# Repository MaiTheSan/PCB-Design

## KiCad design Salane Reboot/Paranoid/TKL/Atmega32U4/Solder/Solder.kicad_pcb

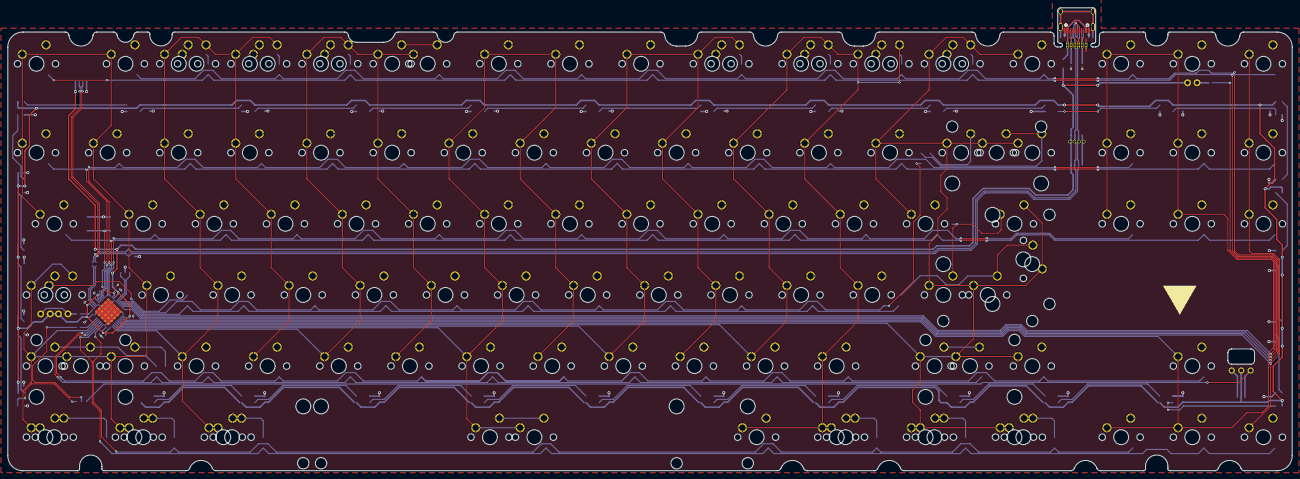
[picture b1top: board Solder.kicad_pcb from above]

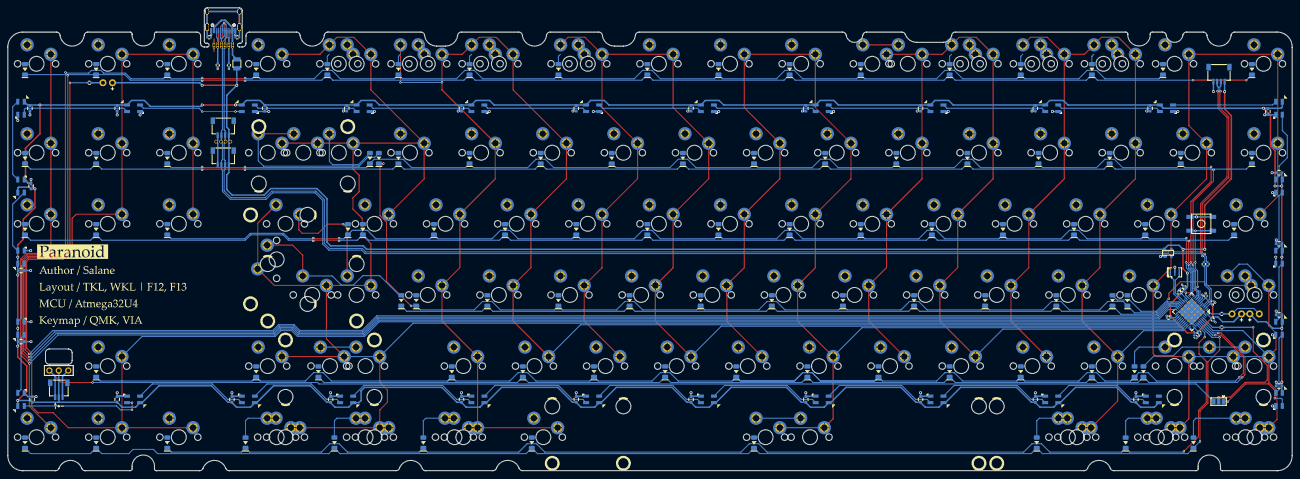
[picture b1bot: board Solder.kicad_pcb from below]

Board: 2 copper layers, 344.0 x 124.0 mm, 299 parts (181 on the bottom side), 164 nets.

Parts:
C1, C3, C4, C5, C6, C8: 0.1uF; C_0402
C2: 1uF; C_0402
C7: 10uF; C_0402
C9, C10, C11, C12, C13, C14, C15, C16, C17, C18, C19, C20, C21, C22, C23, C24, C25, C26, C27, C28, C29, C30, C31, C32, C33, C34, C35, C36, C37, C38: 0.1uF; C_0603
D1: LED; MXOnly-LEDONLY-FLIPPED
D2, D3: LED; MXOnly-LEDONLY
D4, D5, D6, D7, D8, D9, D10, D11, D12, D13, D14, D15, D16, D17, D18, D19, D20, D21, D22, D23, D24, D25, D26, D27, D28, D29, D30, D31, D32, D33, D34, D35, D36, D37, D38, D39, D40, D41, D42, D43, D44, D45, D46, D47, D48, D49, D50, D51, D52, D53, D54, D55, D56, D57, D58, D59, D60, D61, D62, D63, D64, D65, D66, D67, D68, D69, D70, D71, D72, D73, D74, D75, D76, D77, D78, D79, D80, D81, D82, D83, D84, D85, D86, D87, D88, D89, D90, D91, D92, D93, D94: 1N4148W; DIODE_1206_SawnsProjects
F1: 500mA; Fuse_SMD1206_Reflow
J1: Conn_01x06_Female; BreakoutUSB
J2: Suit; JST-SR-4
J3: HIney/Mechlovin; JST-SR-4
J4: Breakout; PinHeader_1x04_P1.27mm_Vertical
J5: Amber TKL; JST-SR-4
J6: RGB JST; JST-SR-3
J7: RGB Breakout; RGB-Header
JP1: Jumper_NC_Dual; SolderJumper-3_P1.3mm_Open_Pad1.0x1.5mm
MX1, MX4, MX17, MX73, MX91, MX99: 1.5U; MXOnly-1.5U-NoLED
MX2, MX3, MX10, MX11, MX12, MX13, MX14, MX15, MX18, MX19, MX20, MX21, MX22, MX24, MX25, MX26, MX27, MX28, MX29, MX30, MX31, MX32, MX33, MX34, MX35, MX36, MX37, MX38, MX39, MX40, MX41, MX42, MX44, MX45, MX46, MX47, MX48, MX50, MX51, MX52, MX53, MX54, MX55, MX56, MX57, MX58, MX59, MX60, MX61, MX62, MX63, MX64, MX65, MX66, MX67, MX68, MX69, MX70, MX72, MX74, MX75, MX76, MX77, MX78, MX80, MX81, MX82, MX83, MX84, MX89, MX92, MX93, MX94, MX95, MX97, MX100, MX101, MX102, MX103, MX104, MX105, MX106, MX107, MX108, MX109, MX110, MX111, MX112: 1U; MXOnly-1U-NoLED
MX5, MX6, MX8, MX16, MX23, MX71, MX79, MX88, MX98: 1.25U; MXOnly-1.25U-NoLED
MX7: 2.25U; MXOnly-2.25U-NoLED
MX9, MX86: 1.75U; MXOnly-1.75U-NoLED
MX43: 7U; MXOnly-7U-ReversedStabilizers-NoLED
MX49: 6.25U; MXOnly-6.25U-ReversedStabilizers-NoLED
MX85: 2.25U; MXOnly-2.25U-ReversedStabilizers-NoLED
MX87: 2.75U; MXOnly-2.75U-NoLED
MX90: ISO; MXOnly-ISO-ROTATED-ReversedStabilizers-NoLED
MX96: 2U; MXOnly-2U-NoLED
R1, R4: 10k; R_0402
R2, R3, R5: 300R; R_0402
R6: 1M; R_0402
R7, R8: 22R; R_0402
R9, R10: 5.1k; R_0402
RGB1, RGB2, RGB3, RGB4, RGB5, RGB6, RGB7, RGB8, RGB9, RGB10, RGB11, RGB12, RGB13, RGB14, RGB15, RGB16, RGB17, RGB18, RGB19, RGB20, RGB21, RGB22, RGB23, RGB24, RGB25, RGB26, RGB27, RGB28, RGB29, RGB30: WS2812B; LED_SK6812MINI_PLCC4_3.5x3.5mm_P1.75mm
SW1: SW_Push; SKQG-1155865-2pin
U1: ATmega32U4-MU; QFN-44-1EP_7x7mm_P0.5mm_EP5.2x5.2mm
U2: PRTR5V0U2X; SOT143B
USB1, USB2: HRO-TYPE-C-31-M-12-Type-C; HRO-TYPE-C-31-M-12-Assembly
Y1: 16MHz; Resonator_SMD_muRata_CSTxExxV-3Pin_3.0x1.1mm

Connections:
+5V: C1.1, C3.1, C4.1, C5.1, C6.1, C7.1, C9.2, C10.2, C11.2, C12.2, C13.2, C14.2, C15.2, C16.2, C17.2, C18.2, C19.1, C20.1, C21.1, C22.1, C23.1, C24.1, C25.1, C26.1, C27.1, C28.1, C29.2, C30.1, C31.2, C32.1, C33.2, C34.1, C35.2, C36.1, C37.2, C38.1, D1.2, D2.2, D3.2, F1.2, J2.1, J3.1, J4.1, J5.1, J6.2, J7.2, R1.1, RGB1.1, RGB2.1, RGB3.1, RGB4.1, RGB5.1, RGB6.1, RGB7.1, RGB8.1, RGB9.1, RGB10.1, RGB11.1, RGB12.1, RGB13.1, RGB14.1, RGB15.1, RGB16.1, RGB17.1, RGB18.1, RGB19.1, RGB20.1, RGB21.1, RGB22.1, RGB23.1, RGB24.1, RGB25.1, RGB26.1, RGB27.1, RGB28.1, RGB29.1, RGB30.1, U1.2, U1.7, U1.14, U1.24, U1.34, U1.44, U2.4
C0: MX1.1, MX2.1, MX3.1, MX4.1, MX5.1, MX6.1, MX7.1, MX8.1, MX9.2, MX10.1, MX11.1, MX12.1, MX13.1, MX14.1, MX15.1, MX16.1, U1.40
C1: MX17.1, MX18.1, MX19.1, MX20.1, MX21.1, MX22.1, MX23.1, MX24.2, MX25.1, MX26.1, MX27.1, MX28.1, MX29.1, MX30.2, U1.32
C2: MX31.1, MX32.1, MX33.1, MX34.1, MX35.1, MX36.2, MX37.1, MX38.1, MX39.1, MX40.1, MX41.1, MX42.1, U1.31
C3: MX43.1, MX44.1, MX45.1, MX46.1, MX47.1, MX48.1, MX49.1, MX50.1, MX51.1, MX52.1, MX53.1, MX54.1, U1.30
C4: MX55.1, MX56.1, MX57.1, MX58.1, MX59.1, MX60.1, MX61.1, MX62.1, MX63.1, MX64.1, MX65.2, U1.29
C5: MX66.1, MX67.1, MX68.1, MX69.1, MX70.1, MX71.1, MX72.2, MX73.1, MX74.1, MX75.1, MX76.1, MX77.1, MX78.1, MX79.1, MX80.2, U1.28
C6: MX81.1, MX82.1, MX83.1, MX84.1, MX85.1, MX86.1, MX87.1, MX88.1, MX89.2, MX90.2, MX91.1, MX92.1, MX93.1, MX94.1, MX95.1, MX96.1, MX97.1, MX98.1, MX99.2, U1.27
C7: MX100.1, MX101.1, MX102.1, MX103.1, MX104.1, MX105.1, MX106.1, MX107.1, MX108.1, U1.26
C8: MX109.1, MX110.1, MX111.1, MX112.1, U1.25
C+: J1.4, J2.3, J3.3, J4.3, J5.3, R8.1, U2.2, USB1.6, USB1.8, USB2.6, USB2.8
C-: J1.3, J2.2, J3.2, J4.2, J5.2, R7.2, U2.3, USB1.5, USB1.7, USB2.5, USB2.7
CC1: J1.2, R9.2, USB1.10, USB2.4
CC2: J1.5, R10.1, USB1.4, USB2.10
Caps: R2.1, U1.1
D+: R8.2, U1.4
D-: R7.1, U1.3
DOUT: J6.3, J7.3, JP1.3
Fuse: F1.1, J1.1, USB1.2, USB1.11, USB2.2, USB2.11
GND: C1.2, C2.1, C3.2, C4.2, C5.2, C6.2, C7.2, C8.2, C9.1, C10.1, C11.1, C12.1, C13.1, C14.1, C15.1, C16.1, C17.1, C18.1, C19.2, C20.2, C21.2, C22.2, C23.2, C24.2, C25.2, C26.2, C27.2, C28.2, C29.1, C30.2, C31.1, C32.2, C33.1, C34.2, C35.1, C36.2, C37.1, C38.2, J1.6, J2.4, J3.4, J4.4, J5.4, J6.1, J7.1, R4.1, R6.1, R9.1, R10.2, RGB1.3, RGB2.3, RGB3.3, RGB4.3, RGB5.3, RGB6.3, RGB7.3, RGB8.3, RGB9.3, RGB10.3, RGB11.3, RGB12.3, RGB13.3, RGB14.3, RGB15.3, RGB16.3, RGB17.3, RGB18.3, RGB19.3, RGB20.3, RGB21.3, RGB22.3, RGB23.3, RGB24.3, RGB25.3, RGB26.3, RGB27.3, RGB28.3, RGB29.3, RGB30.3, SW1.1, U1.5, U1.15, U1.23, U1.35, U1.43, U1.45, U2.1, USB1.1, USB1.12, USB2.1, USB2.12, Y1.2
unnamed: C2.2, U1.6
unnamed: D1.1, D2.1, R2.2
unnamed: D3.1, R3.2
unnamed: D4.2, MX2.2
unnamed: D5.2, MX3.2
unnamed: D6.2, MX4.2
unnamed: D7.2, MX5.2, MX9.1
unnamed: D8.2, MX6.2, MX7.2
unnamed: D9.2, MX1.2, MX8.2
unnamed: D10.2, MX11.2
unnamed: D11.2, MX12.2
unnamed: D12.2, MX13.2
unnamed: D13.2, MX14.2
unnamed: D14.2, MX15.2
unnamed: D15.2, MX10.2, MX16.2
unnamed: D16.2, MX18.2, MX24.1
unnamed: D17.2, MX19.2
unnamed: D18.2, MX20.2
unnamed: D19.2, MX21.2
unnamed: D20.2, MX22.2
unnamed: D21.2, MX17.2, MX23.2
unnamed: D22.2, MX25.2, MX30.1
unnamed: D23.2, MX26.2
unnamed: D24.2, MX27.2
unnamed: D25.2, MX28.2
unnamed: D26.2, MX29.2
unnamed: D27.2, MX31.2, MX36.1
unnamed: D28.2, MX32.2
unnamed: D29.2, MX33.2
unnamed: D30.2, MX34.2
unnamed: D31.2, MX35.2
unnamed: D32.2, MX37.2, MX38.2
unnamed: D33.2, MX39.2
unnamed: D34.2, MX40.2
unnamed: D35.2, MX41.2
unnamed: D36.2, MX42.2
unnamed: D37.2, MX44.2
unnamed: D38.2, MX45.2
unnamed: D39.2, MX46.2
unnamed: D40.2, MX47.2
unnamed: D41.2, MX48.2
unnamed: D42.2, MX43.2, MX49.2
unnamed: D43.2, MX50.2
unnamed: D44.2, MX51.2
unnamed: D45.2, MX52.2
unnamed: D46.2, MX53.2
unnamed: D47.2, MX54.2
unnamed: D48.2, MX55.2
unnamed: D49.2, MX56.2
unnamed: D50.2, MX57.2
unnamed: D51.2, MX58.2
unnamed: D52.2, MX59.2
unnamed: D53.2, MX60.2, MX65.1
unnamed: D54.2, MX61.2
unnamed: D55.2, MX62.2
unnamed: D56.2, MX63.2
unnamed: D57.2, MX64.2
unnamed: D58.2, MX66.2, MX72.1
unnamed: D59.2, MX67.2
unnamed: D60.2, MX68.2
unnamed: D61.2, MX69.2
unnamed: D62.2, MX70.2
unnamed: D63.2, MX71.2
unnamed: D64.2, MX74.2, MX80.1
unnamed: D65.2, MX75.2
unnamed: D66.2, MX76.2
unnamed: D67.2, MX77.2
unnamed: D68.2, MX78.2
unnamed: D69.2, MX73.2, MX79.2
unnamed: D70.2, MX82.2, MX89.1
unnamed: D71.2, MX83.2
unnamed: D72.2, MX84.2
unnamed: D73.2, MX85.2, MX90.1
unnamed: D74.2, MX86.2, MX87.2
unnamed: D75.2, MX81.2, MX88.2
unnamed: D76.2, MX92.2
unnamed: D77.2, MX93.2
unnamed: D78.2, MX94.2, MX99.1
unnamed: D79.2, MX95.2, MX96.2
unnamed: D80.2, MX97.2
unnamed: D81.2, MX91.2, MX98.2
unnamed: D82.2, MX100.2
unnamed: D83.2, MX101.2
unnamed: D84.2, MX102.2
unnamed: D85.2, MX103.2
unnamed: D86.2, MX104.2
unnamed: D87.2, MX105.2
unnamed: D88.2, MX106.2
unnamed: D89.2, MX107.2
unnamed: D90.2, MX108.2
unnamed: D91.2, MX109.2
unnamed: D92.2, MX110.2
unnamed: D93.2, MX111.2
unnamed: D94.2, MX112.2
unnamed: R1.2, SW1.2, U1.13
unnamed: R4.2, U1.33
unnamed: R5.2, U1.41
unnamed: RGB1.2, RGB4.4
unnamed: RGB2.2, RGB5.4
unnamed: RGB3.2, RGB6.4
unnamed: RGB4.2, RGB7.4
unnamed: RGB5.2, RGB8.4
unnamed: RGB6.2, RGB9.4
unnamed: RGB10.2, RGB13.4
unnamed: RGB7.2, RGB10.4
unnamed: RGB11.2, RGB14.4
unnamed: RGB8.2, RGB11.4
unnamed: RGB9.2, RGB12.4
unnamed: RGB14.2, RGB15.4
unnamed: RGB15.2, RGB16.4
unnamed: RGB16.2, RGB17.4
unnamed: RGB17.2, RGB18.4
unnamed: RGB18.2, RGB19.4
unnamed: RGB3.4, RGB20.2
unnamed: RGB21.2, RGB22.4
unnamed: RGB22.2, RGB23.4
unnamed: RGB23.2, RGB24.4
unnamed: RGB24.2, RGB25.4
unnamed: RGB25.2, RGB26.4
unnamed: RGB26.2, RGB27.4
unnamed: RGB27.2, RGB28.4
unnamed: RGB28.2, RGB29.4
unnamed: RGB29.2, RGB30.4
unnamed: U1.16, Y1.3
unnamed: U1.17, Y1.1
R0: D4.1, D16.1, D27.1, D37.1, D48.1, D58.1, D70.1, D86.1, D91.1, U1.21
R1: D10.1, D22.1, D32.1, D43.1, D53.1, D64.1, D76.1, D82.1, U1.22
R2: D5.1, D17.1, D28.1, D38.1, D49.1, D59.1, D71.1, D87.1, D92.1, U1.9
R3: D11.1, D23.1, D33.1, D44.1, D54.1, D65.1, D77.1, D83.1, U1.10
R4: D6.1, D18.1, D29.1, D39.1, D50.1, D60.1, D72.1, D88.1, D93.1, U1.11
R5: D12.1, D24.1, D34.1, D45.1, D55.1, D66.1, D78.1, D84.1, U1.12
R6: D7.1, D19.1, D30.1, D40.1, D51.1, D61.1, D73.1, U1.19
R7: D13.1, D25.1, D35.1, D46.1, D56.1, D67.1, D79.1, U1.18
R8: D8.1, D20.1, D31.1, D41.1, D52.1, D62.1, D74.1, U1.39
R9: D14.1, D26.1, D36.1, D47.1, D57.1, D68.1, D80.1, D89.1, U1.38
R10: D9.1, D21.1, D42.1, D63.1, D75.1, D90.1, D94.1, U1.37
R11: D15.1, D69.1, D81.1, D85.1, U1.36
RGB: JP1.2, R5.1
Scroll: R3.1, U1.20
Shiled: C8.1, R6.2, USB1.13, USB2.13
Strip1: RGB2.4, RGB13.2
Strip2: RGB19.2, RGB20.4
Strip3: RGB12.2, RGB21.4
Underglow: JP1.1, RGB1.4

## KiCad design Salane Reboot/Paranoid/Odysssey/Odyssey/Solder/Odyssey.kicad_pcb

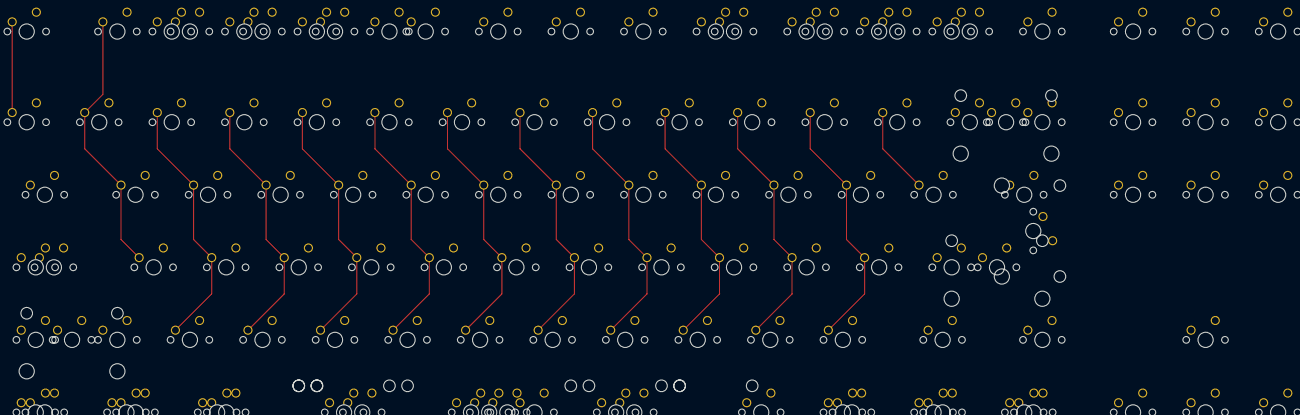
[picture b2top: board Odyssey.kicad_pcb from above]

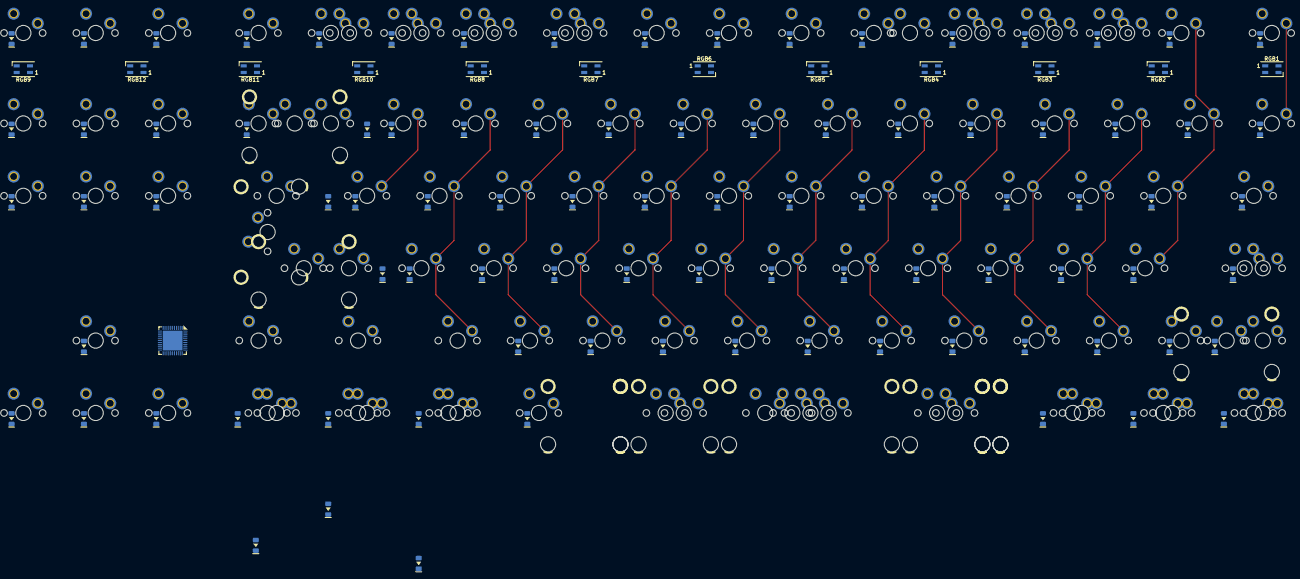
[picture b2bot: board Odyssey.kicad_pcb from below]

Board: 2 copper layers, 220 parts (103 on the bottom side), 118 nets.

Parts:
D1, D2, D3, D4, D5, D6, D7, D8, D9, D10, D11, D12, D13, D14, D15, D16, D17, D18, D19, D20, D21, D22, D23, D24, D25, D26, D27, D28, D29, D30, D31, D32, D33, D34, D35, D36, D37, D38, D39, D40, D41, D42, D43, D44, D45, D46, D47, D48, D49, D50, D51, D52, D53, D54, D55, D56, D57, D58, D59, D60, D61, D62, D63, D64, D65, D66, D67, D68, D69, D70, D71, D72, D73, D74, D75, D76, D77, D78, D79, D80, D81, D82, D83, D91, D92, D93, D94, D95, D96, D97: 1N4148W; DIODE_1206_SawnsProjects
MX1, MX2, MX3, MX4, MX5, MX6, MX7, MX8, MX9, MX10, MX11, MX12, MX13, MX14, MX15, MX16, MX17, MX18, MX19, MX20, MX21, MX22, MX23, MX24, MX25, MX26, MX27, MX28, MX29, MX30, MX31, MX32, MX33, MX34, MX36, MX37, MX38, MX39, MX40, MX41, MX42, MX43, MX44, MX45, MX46, MX47, MX49, MX50, MX51, MX53, MX54, MX55, MX56, MX57, MX58, MX59, MX60, MX61, MX62, MX63, MX65, MX67, MX68, MX69, MX70, MX71, MX72, MX73, MX74, MX75, MX76, MX77, MX78, MX91, MX95, MX96, MX97, MX99, MX102, MX107, MX114, MX115, MX116, MX117, MX118, MX119, MX120, MX121: 1U; MXOnly-1U-NoLED
MX35, MX48, MX98, MX100, MX101, MX103: 1.5U; MXOnly-1.5U-NoLED
MX52, MX79: 1.75U; MXOnly-1.75U-NoLED
MX64, MX83, MX86, MX108: 2.25U; MXOnly-2.25U-NoLED
MX66, MX80, MX81, MX82, MX85, MX88, MX89, MX92, MX93, MX94, MX109: 1.25U; MXOnly-1.25U-NoLED
MX84, MX87: 2.75U; MXOnly-2.75U-NoLED
MX90: 6.25U; MXOnly-6.25U-NoLED
MX104: 7U; MXOnly-7U-NoLED
MX105: 2U; MXOnly-2U-NoLED
MX106: ISO; MXOnly-ISO-ROTATED-ReversedStabilizers-NoLED
RGB1, RGB2, RGB3, RGB4, RGB5, RGB6, RGB7, RGB8, RGB9, RGB10, RGB11, RGB12: SK6812MINI; LED_SK6812MINI_PLCC4_3.5x3.5mm_P1.75mm
U1: ATmega32U4-MU; QFN-44-1EP_7x7mm_P0.5mm_EP5.2x5.2mm

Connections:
unnamed: D1.2, MX1.2
unnamed: D2.2, MX2.2
unnamed: D3.2, MX3.1, MX114.2
unnamed: D4.2, MX4.1, MX115.2
unnamed: D5.2, MX5.1, MX116.2
unnamed: D6.2, MX6.1, MX117.2
unnamed: D7.2, MX7.2
unnamed: D8.2, MX8.2
unnamed: D9.2, MX9.2
unnamed: D10.2, MX10.1, MX118.2
unnamed: D11.2, MX11.2, MX119.1
unnamed: D12.2, MX12.2, MX120.1
unnamed: D13.2, MX13.2, MX121.1
unnamed: D14.2, MX14.2
unnamed: D15.2, MX15.2
unnamed: D16.2, MX16.2
unnamed: D17.2, MX17.2
unnamed: D18.2, MX18.2
unnamed: D19.2, MX19.2
unnamed: D20.2, MX20.2
unnamed: D21.2, MX21.2
unnamed: D22.2, MX22.2
unnamed: D23.2, MX23.2
unnamed: D24.2, MX24.2
unnamed: D25.2, MX25.2
unnamed: D26.2, MX26.2
unnamed: D27.2, MX27.2
unnamed: D28.2, MX28.2
unnamed: D29.2, MX29.2
unnamed: D30.2, MX30.2
unnamed: D31.2, MX31.1, MX105.1
unnamed: D32.2, MX32.2
unnamed: D33.2, MX33.2
unnamed: D34.2, MX34.2
unnamed: D35.2, MX35.2
unnamed: D36.2, MX36.2
unnamed: D37.2, MX37.2
unnamed: D38.2, MX38.2
unnamed: D39.2, MX39.2
unnamed: D40.2, MX40.2
unnamed: D41.2, MX41.2
unnamed: D42.2, MX42.2
unnamed: D43.2, MX43.2
unnamed: D44.2, MX44.2
unnamed: D45.2, MX45.2
unnamed: D46.2, MX46.2
unnamed: D47.2, MX47.2
unnamed: D48.2, MX48.2
unnamed: D49.2, MX49.2
unnamed: D50.2, MX50.2
unnamed: D51.2, MX51.2
unnamed: D52.2, MX52.1, MX109.2
unnamed: D53.2, MX53.2
unnamed: D54.2, MX54.2
unnamed: D55.2, MX55.2
unnamed: D56.2, MX56.2
unnamed: D57.2, MX57.2
unnamed: D58.2, MX58.2
unnamed: D59.2, MX59.2
unnamed: D60.2, MX60.2
unnamed: D61.2, MX61.2
unnamed: D62.2, MX62.2
unnamed: D63.2, MX63.2
unnamed: D64.2, MX64.2
unnamed: D65.2, MX65.1
unnamed: D66.2, MX66.2, MX108.2
unnamed: D67.2, MX67.2
unnamed: D68.2, MX68.2
unnamed: D69.2, MX69.2
unnamed: D70.2, MX70.2
unnamed: D71.2, MX71.2
unnamed: D72.2, MX72.2
unnamed: D73.2, MX73.2
unnamed: D74.2, MX74.2
unnamed: D75.2, MX75.2
unnamed: D76.2, MX76.2
unnamed: D77.2, MX77.2
unnamed: D78.2, MX79.2
unnamed: D79.2, MX78.2
unnamed: D80.2, MX80.2, MX98.2
unnamed: D81.2, MX81.2, MX99.2
unnamed: D82.2, MX82.2, MX100.2
unnamed: D83.2, MX85.2
unnamed: D91.2, MX94.2, MX101.2
unnamed: D92.2, MX92.2, MX102.2
unnamed: D93.2, MX93.2, MX103.2
unnamed: D94.2, MX91.2
unnamed: D95.2, MX95.2
unnamed: D96.2, MX96.2
unnamed: D97.2, MX97.2
unnamed: MX1.1, MX2.1, MX18.1, MX19.1, MX35.1, MX36.1, MX52.2, MX53.1, MX66.1, MX67.1, MX80.1, MX81.1, MX98.1, MX99.1, MX108.1, MX109.1
unnamed: MX9.1, MX10.2, MX26.1, MX27.1, MX43.1, MX44.1, MX60.1, MX61.1, MX74.1, MX75.1, MX118.1
unnamed: MX15.1, MX16.1, MX32.1, MX33.1, MX49.1, MX50.1, MX91.1, MX95.1, MX96.1
unnamed: MX17.1, MX34.1, MX51.1, MX97.1
unnamed: MX7.1, MX8.1, MX24.1, MX25.1, MX41.1, MX42.1, MX58.1, MX59.1, MX72.1, MX73.1
unnamed: MX83.1, MX87.2
unnamed: MX83.2, MX87.1
unnamed: MX84.1, MX86.2
unnamed: MX84.2, MX86.1
unnamed: MX3.2, MX4.2, MX20.1, MX21.1, MX37.1, MX38.1, MX54.1, MX55.1, MX68.1, MX69.1, MX82.1, MX100.1, MX114.1, MX115.1
unnamed: MX11.1, MX12.1, MX28.1, MX29.1, MX45.1, MX46.1, MX62.1, MX63.1, MX76.1, MX77.1, MX85.1, MX94.1, MX101.1, MX119.2, MX120.2
unnamed: MX13.1, MX14.1, MX30.1, MX31.2, MX47.1, MX48.1, MX64.1, MX65.2, MX78.1, MX79.1, MX92.1, MX93.1, MX102.1, MX103.1, MX105.2, MX121.2
unnamed: MX88.2, MX89.2, MX90.1, MX104.1
unnamed: MX88.1, MX89.1, MX90.2, MX104.2
unnamed: MX5.2, MX6.2, MX22.1, MX23.1, MX39.1, MX40.1, MX56.1, MX57.1, MX70.1, MX71.1, MX116.1, MX117.1
unnamed: RGB1.1, RGB2.3
unnamed: RGB2.1, RGB3.3
unnamed: RGB3.1, RGB4.3
unnamed: RGB4.1, RGB5.3
unnamed: RGB5.1, RGB6.3
unnamed: RGB6.1, RGB7.3
unnamed: RGB7.1, RGB8.3
unnamed: RGB10.1, RGB11.3
unnamed: RGB8.1, RGB10.3
unnamed: RGB11.1, RGB12.3
unnamed: U1.14, U1.34
unnamed: U1.15, U1.23, U1.35, U1.43, U1.45
unnamed: U1.24, U1.44

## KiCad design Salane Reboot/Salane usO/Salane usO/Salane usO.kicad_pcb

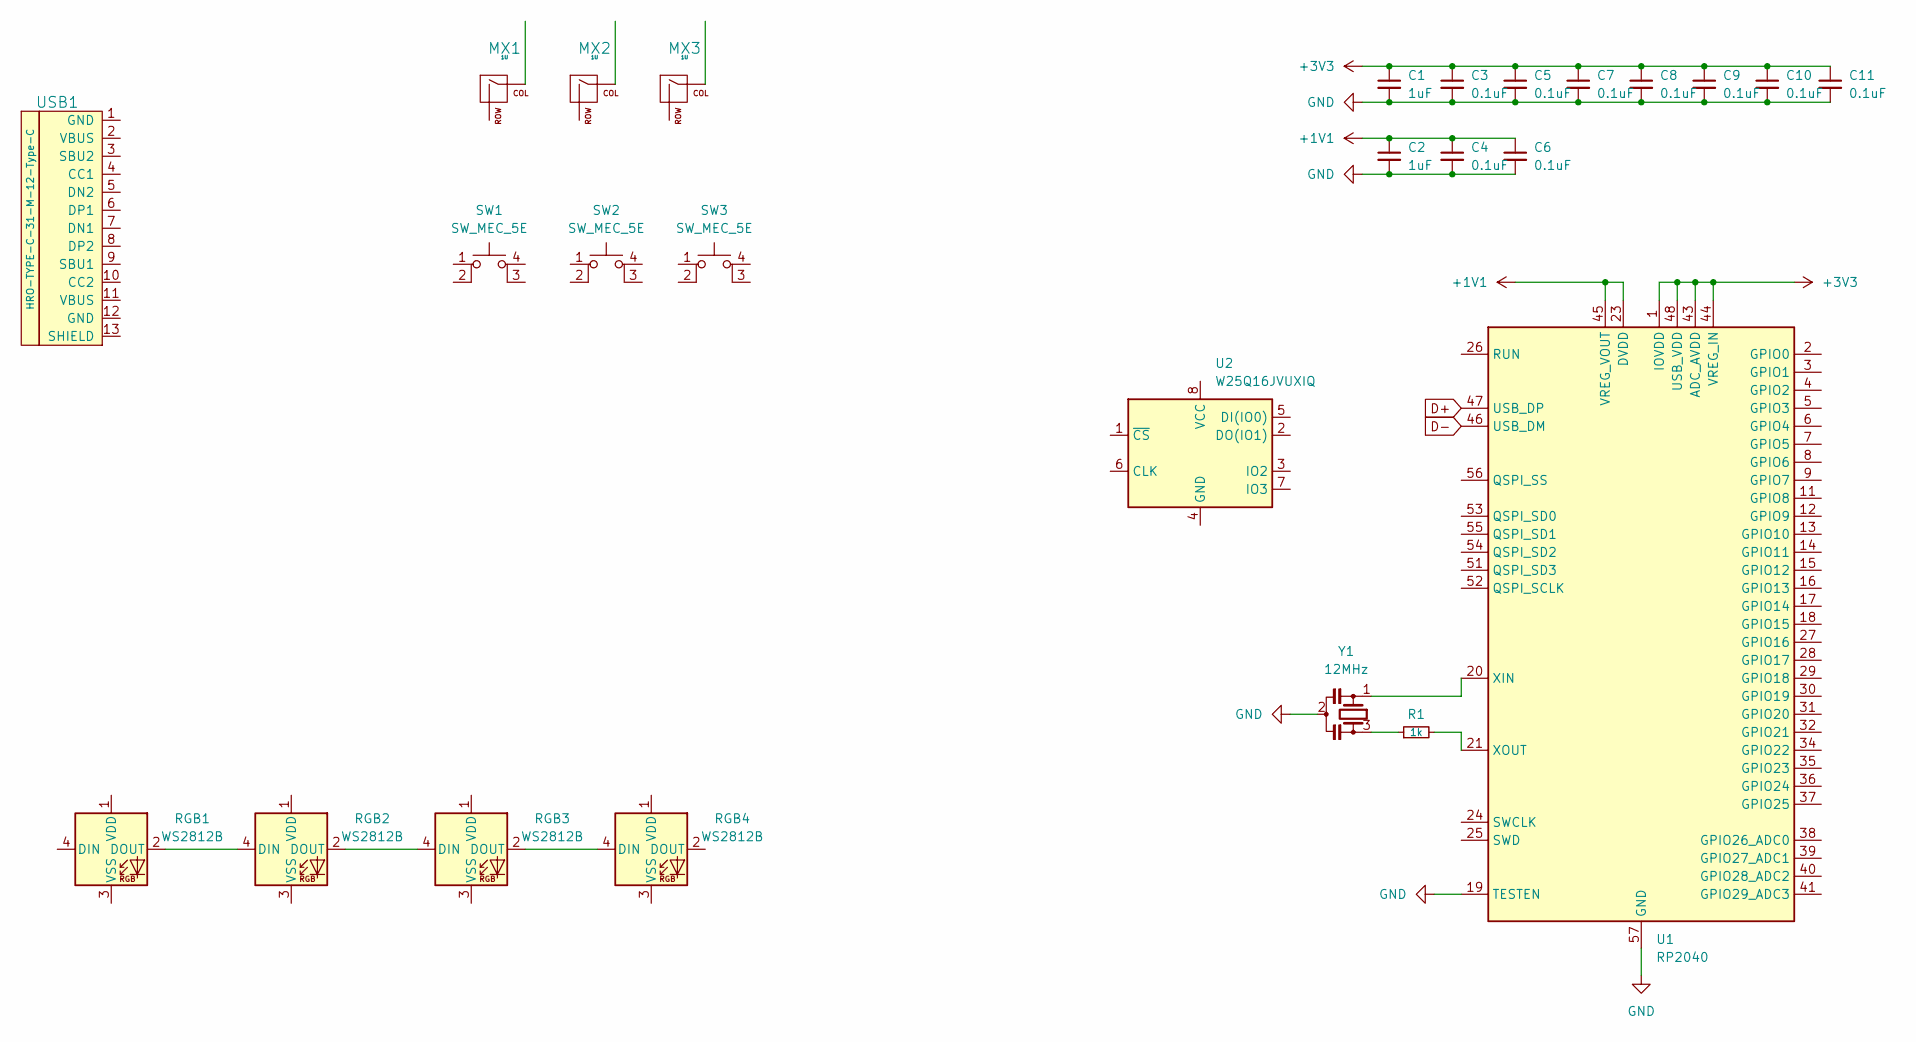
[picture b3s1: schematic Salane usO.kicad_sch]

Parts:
C1, C2: 1uF; C_0402
C3, C4, C5, C6, C7, C8, C9, C10, C11: 0.1uF; C_0402
MX1, MX2, MX3: 1U; MXOnly-1U-Hotswap-Sawns
R1: 1k; R_0402
RGB1, RGB2, RGB3, RGB4: WS2812B; LED_WS2812B_PLCC4_5.0x5.0mm_P3.2mm
SW1, SW2, SW3: SW_MEC_5E; PushButton_6x6mm_TH
U1: RP2040; QFN-56-1EP_7x7mm_P0.4mm_EP3.2x3.2mm
U2: W25Q16JVUXIQ; SON-8-1EP_3x2mm_P0.5mm_EP1.4x1.6mm
USB1: HRO-TYPE-C-31-M-12-Type-C; HRO-TYPE-C-31-M-12-Assembly
Y1: 12MHz; Resonator_SMD_Murata_CSTxExxV-3Pin_3.0x1.1mm

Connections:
+1V1: C2.1, C4.1, C6.1, U1.23 (DVDD), U1.45 (VREG_VOUT), U1.50 (DVDD)
+3V3: C1.1, C3.1, C5.1, C7.1, C8.1, C9.1, C10.1, C11.1, U1.1 (IOVDD), U1.10 (IOVDD), U1.22 (IOVDD), U1.33 (IOVDD), U1.42 (IOVDD), U1.43 (ADC_AVDD), U1.44 (VREG_IN), U1.48 (USB_VDD), U1.49 (IOVDD)
D+: U1.47 (USB_DP)
D-: U1.46 (USB_DM)
GND: C1.2, C2.2, C3.2, C4.2, C5.2, C6.2, C7.2, C8.2, C9.2, C10.2, C11.2, U1.19 (TESTEN), U1.57 (GND), Y1.2
unnamed: R1.1, Y1.3
unnamed: RGB1.2 (DOUT), RGB2.4 (DIN)
unnamed: RGB2.2 (DOUT), RGB3.4 (DIN)
unnamed: RGB3.2 (DOUT), RGB4.4 (DIN)
unnamed: U1.20 (XIN), Y1.1
unnamed: R1.2, U1.21 (XOUT)

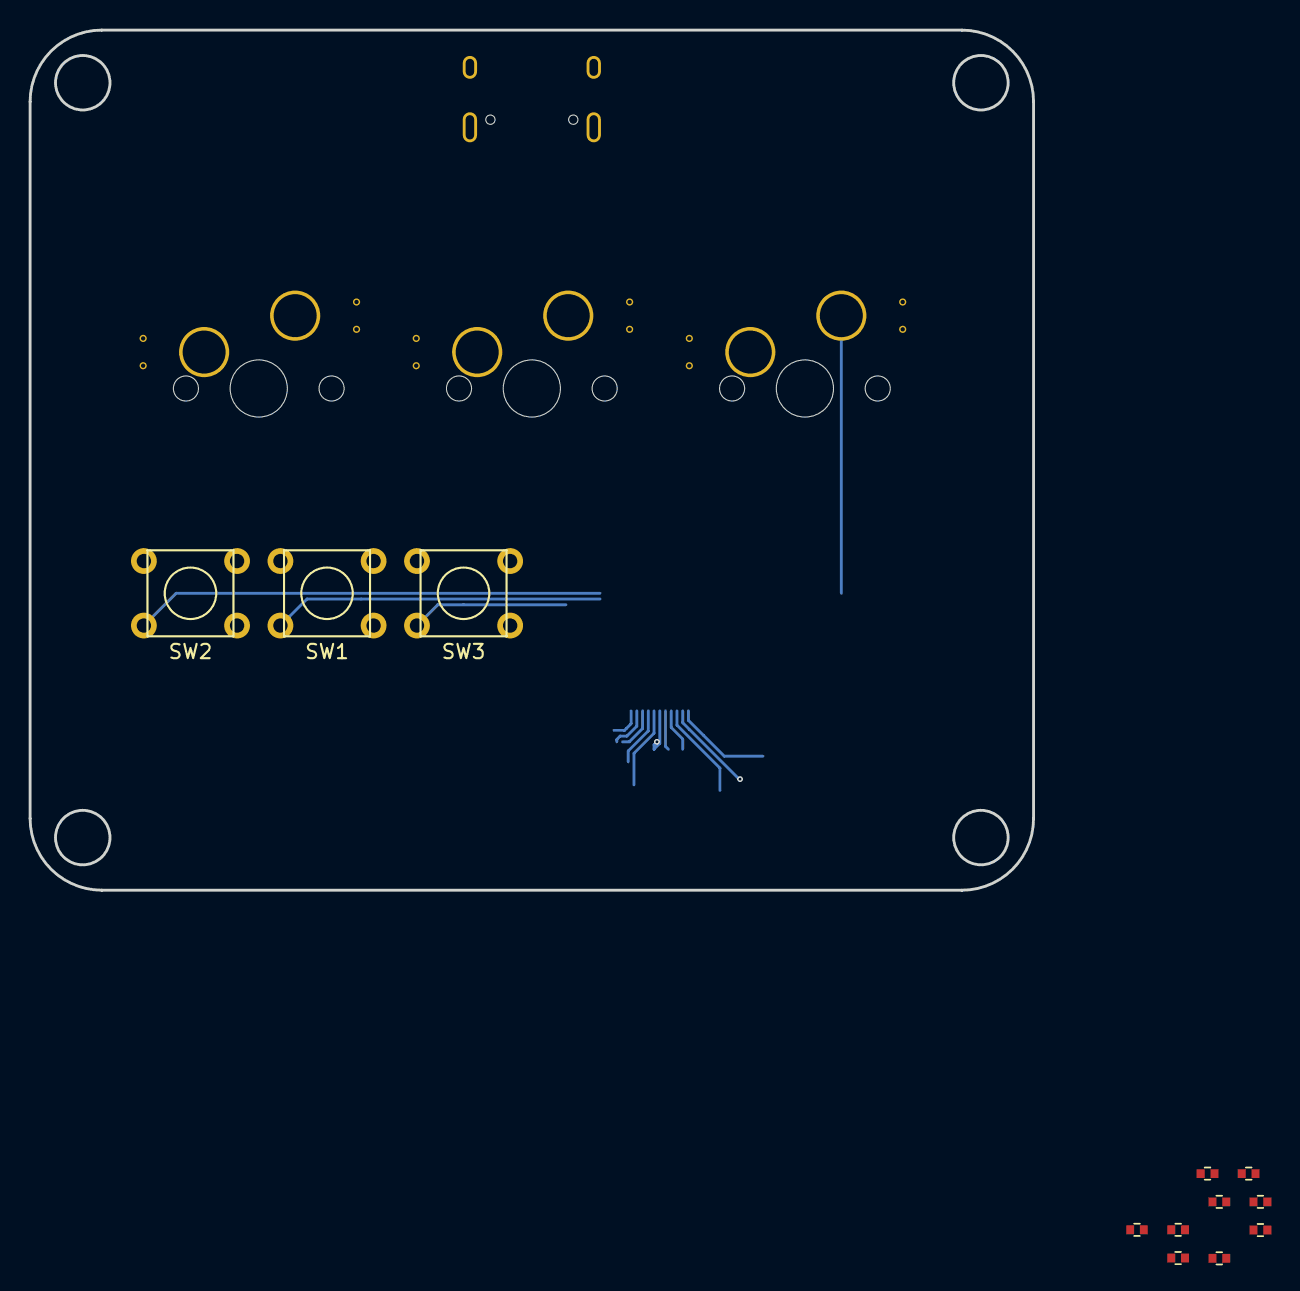
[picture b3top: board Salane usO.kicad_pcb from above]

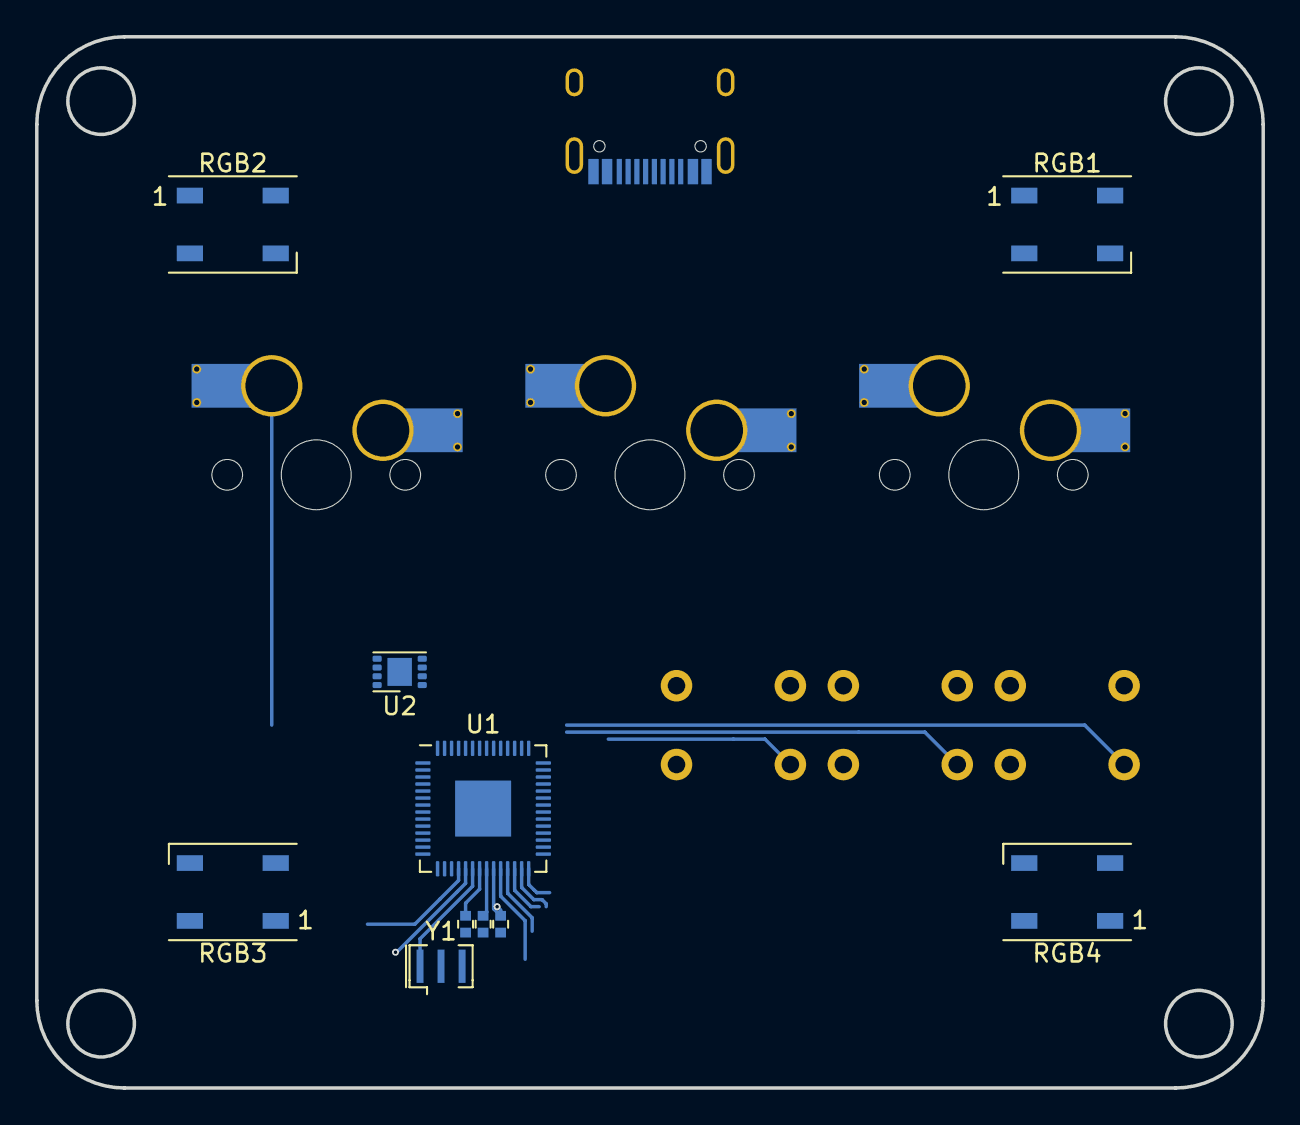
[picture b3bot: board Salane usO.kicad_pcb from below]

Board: 2 copper layers, 70.0 x 60.0 mm, 26 parts (11 on the bottom side), 9 nets.

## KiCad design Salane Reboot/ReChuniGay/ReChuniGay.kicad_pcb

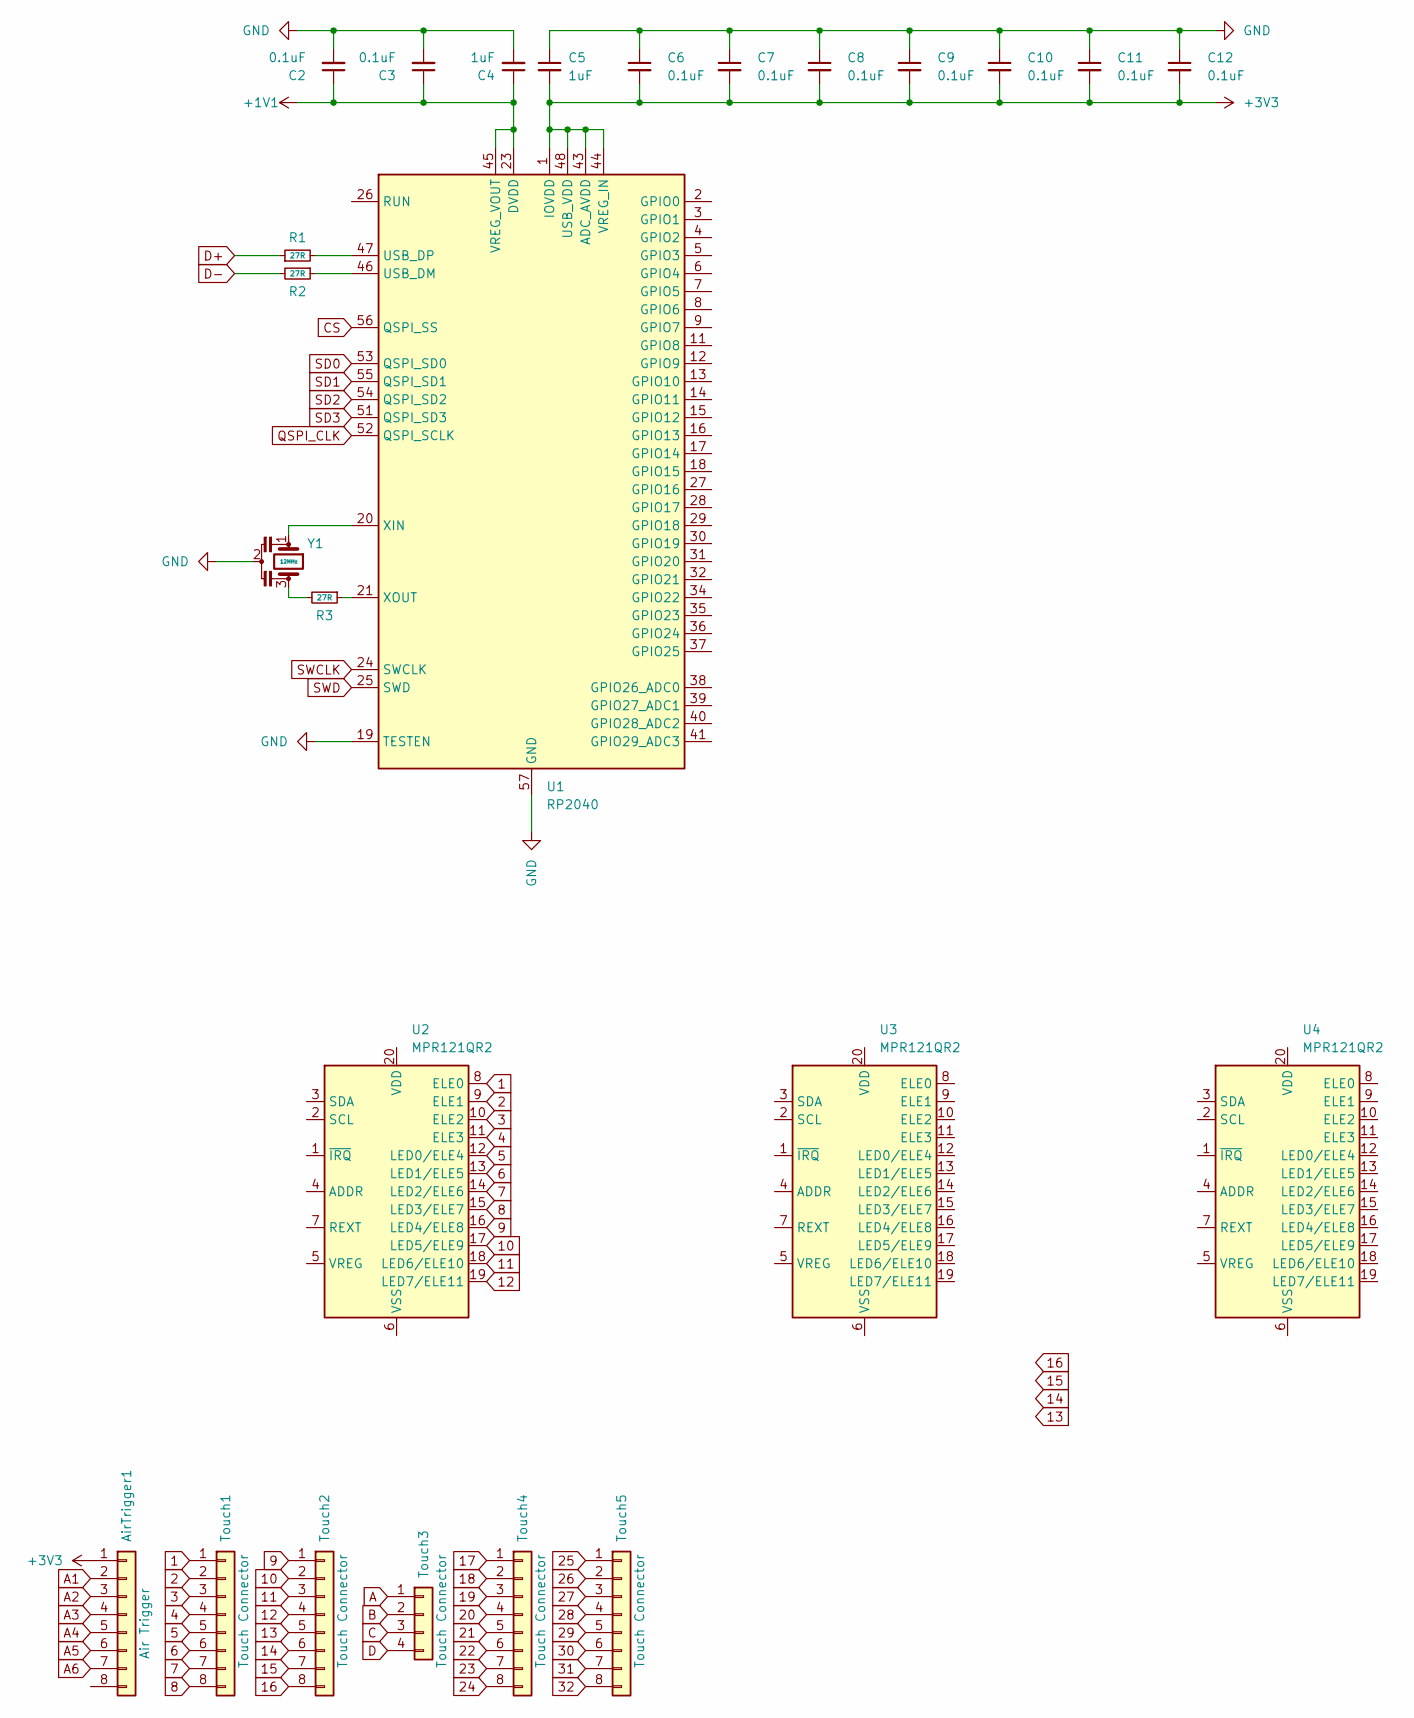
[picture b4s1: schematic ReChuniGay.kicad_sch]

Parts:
AirTrigger1: Air Trigger; JST_XH_S8B-XH-A-1_1x08_P2.50mm_Horizontal
C2, C3, C6, C7, C8, C9, C10, C11, C12: 0.1uF; C_0402
C4, C5: 1uF; C_0402
R1, R2, R3: 27R; R_0402
Touch1, Touch2, Touch4, Touch5: Touch Connector; JST_XH_S8B-XH-A-1_1x08_P2.50mm_Horizontal
Touch3: Touch Connector; JST_XH_S5B-XH-A-1_1x05_P2.50mm_Horizontal
U1: RP2040; RP2040-QFN-56
U2, U3, U4: MPR121QR2; UQFN-20_3x3mm_P0.4mm
Y1: 12MHz

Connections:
1: Touch1.1, U2.8 (ELE0)
2: Touch1.2, U2.9 (ELE1)
3: Touch1.3, U2.10 (ELE2)
4: Touch1.4, U2.11 (ELE3)
5: Touch1.5, U2.12 (LED0/ELE4)
6: Touch1.6, U2.13 (LED1/ELE5)
7: Touch1.7, U2.14 (LED2/ELE6)
8: Touch1.8, U2.15 (LED3/ELE7)
9: Touch2.1, U2.16 (LED4/ELE8)
10: Touch2.2, U2.17 (LED5/ELE9)
11: Touch2.3, U2.18 (LED6/ELE10)
12: Touch2.4, U2.19 (LED7/ELE11)
13: Touch2.5
14: Touch2.6
15: Touch2.7
16: Touch2.8
17: Touch4.1
18: Touch4.2
19: Touch4.3
20: Touch4.4
21: Touch4.5
22: Touch4.6
23: Touch4.7
24: Touch4.8
25: Touch5.1
26: Touch5.2
27: Touch5.3
28: Touch5.4
29: Touch5.5
30: Touch5.6
31: Touch5.7
32: Touch5.8
+1V1: C2.1, C3.1, C4.1, U1.23 (DVDD), U1.45 (VREG_VOUT), U1.50 (DVDD)
+3V3: AirTrigger1.1, C5.2, C6.2, C7.2, C8.2, C9.2, C10.2, C11.2, C12.2, U1.1 (IOVDD), U1.10 (IOVDD), U1.22 (IOVDD), U1.33 (IOVDD), U1.42 (IOVDD), U1.43 (ADC_AVDD), U1.44 (VREG_IN), U1.48 (USB_VDD), U1.49 (IOVDD); also elsewhere on the board
A: Touch3.1
A1: AirTrigger1.2; also elsewhere on the board
A2: AirTrigger1.3; also elsewhere on the board
A3: AirTrigger1.4; also elsewhere on the board
A4: AirTrigger1.5; also elsewhere on the board
A5: AirTrigger1.6; also elsewhere on the board
A6: AirTrigger1.7; also elsewhere on the board
B: Touch3.2
C: Touch3.3
CS: U1.56 (QSPI_SS)
D: Touch3.4
D+: R1.1
D-: R2.2
GND: C2.2, C3.2, C4.2, C5.1, C6.1, C7.1, C8.1, C9.1, C10.1, C11.1, C12.1, U1.19 (TESTEN), U1.57 (GND), Y1.2
unnamed: R1.2, U1.47 (USB_DP)
unnamed: R2.1, U1.46 (USB_DM)
unnamed: R3.1, U1.21 (XOUT)
unnamed: R3.2, Y1.3
unnamed: U1.20 (XIN), Y1.1
QSPI_CLK: U1.52 (QSPI_SCLK)
SD0: U1.53 (QSPI_SD0)
SD1: U1.55 (QSPI_SD1)
SD2: U1.54 (QSPI_SD2)
SD3: U1.51 (QSPI_SD3)
SWCLK: U1.24 (SWCLK)
SWD: U1.25 (SWD)

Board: 2 copper layers, 25 parts (0 on the bottom side), 24 nets, no tracks yet.

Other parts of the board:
AirTrigger1#2: Air Trigger; JST_XH_S8B-XH-A-1_1x08_P2.50mm_Horizontal

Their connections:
+3V3: AirTrigger1#2.1; also elsewhere on the board
A1: AirTrigger1#2.2; also elsewhere on the board
A2: AirTrigger1#2.3; also elsewhere on the board
A3: AirTrigger1#2.4; also elsewhere on the board
A4: AirTrigger1#2.5; also elsewhere on the board
A5: AirTrigger1#2.6; also elsewhere on the board
A6: AirTrigger1#2.7; also elsewhere on the board
